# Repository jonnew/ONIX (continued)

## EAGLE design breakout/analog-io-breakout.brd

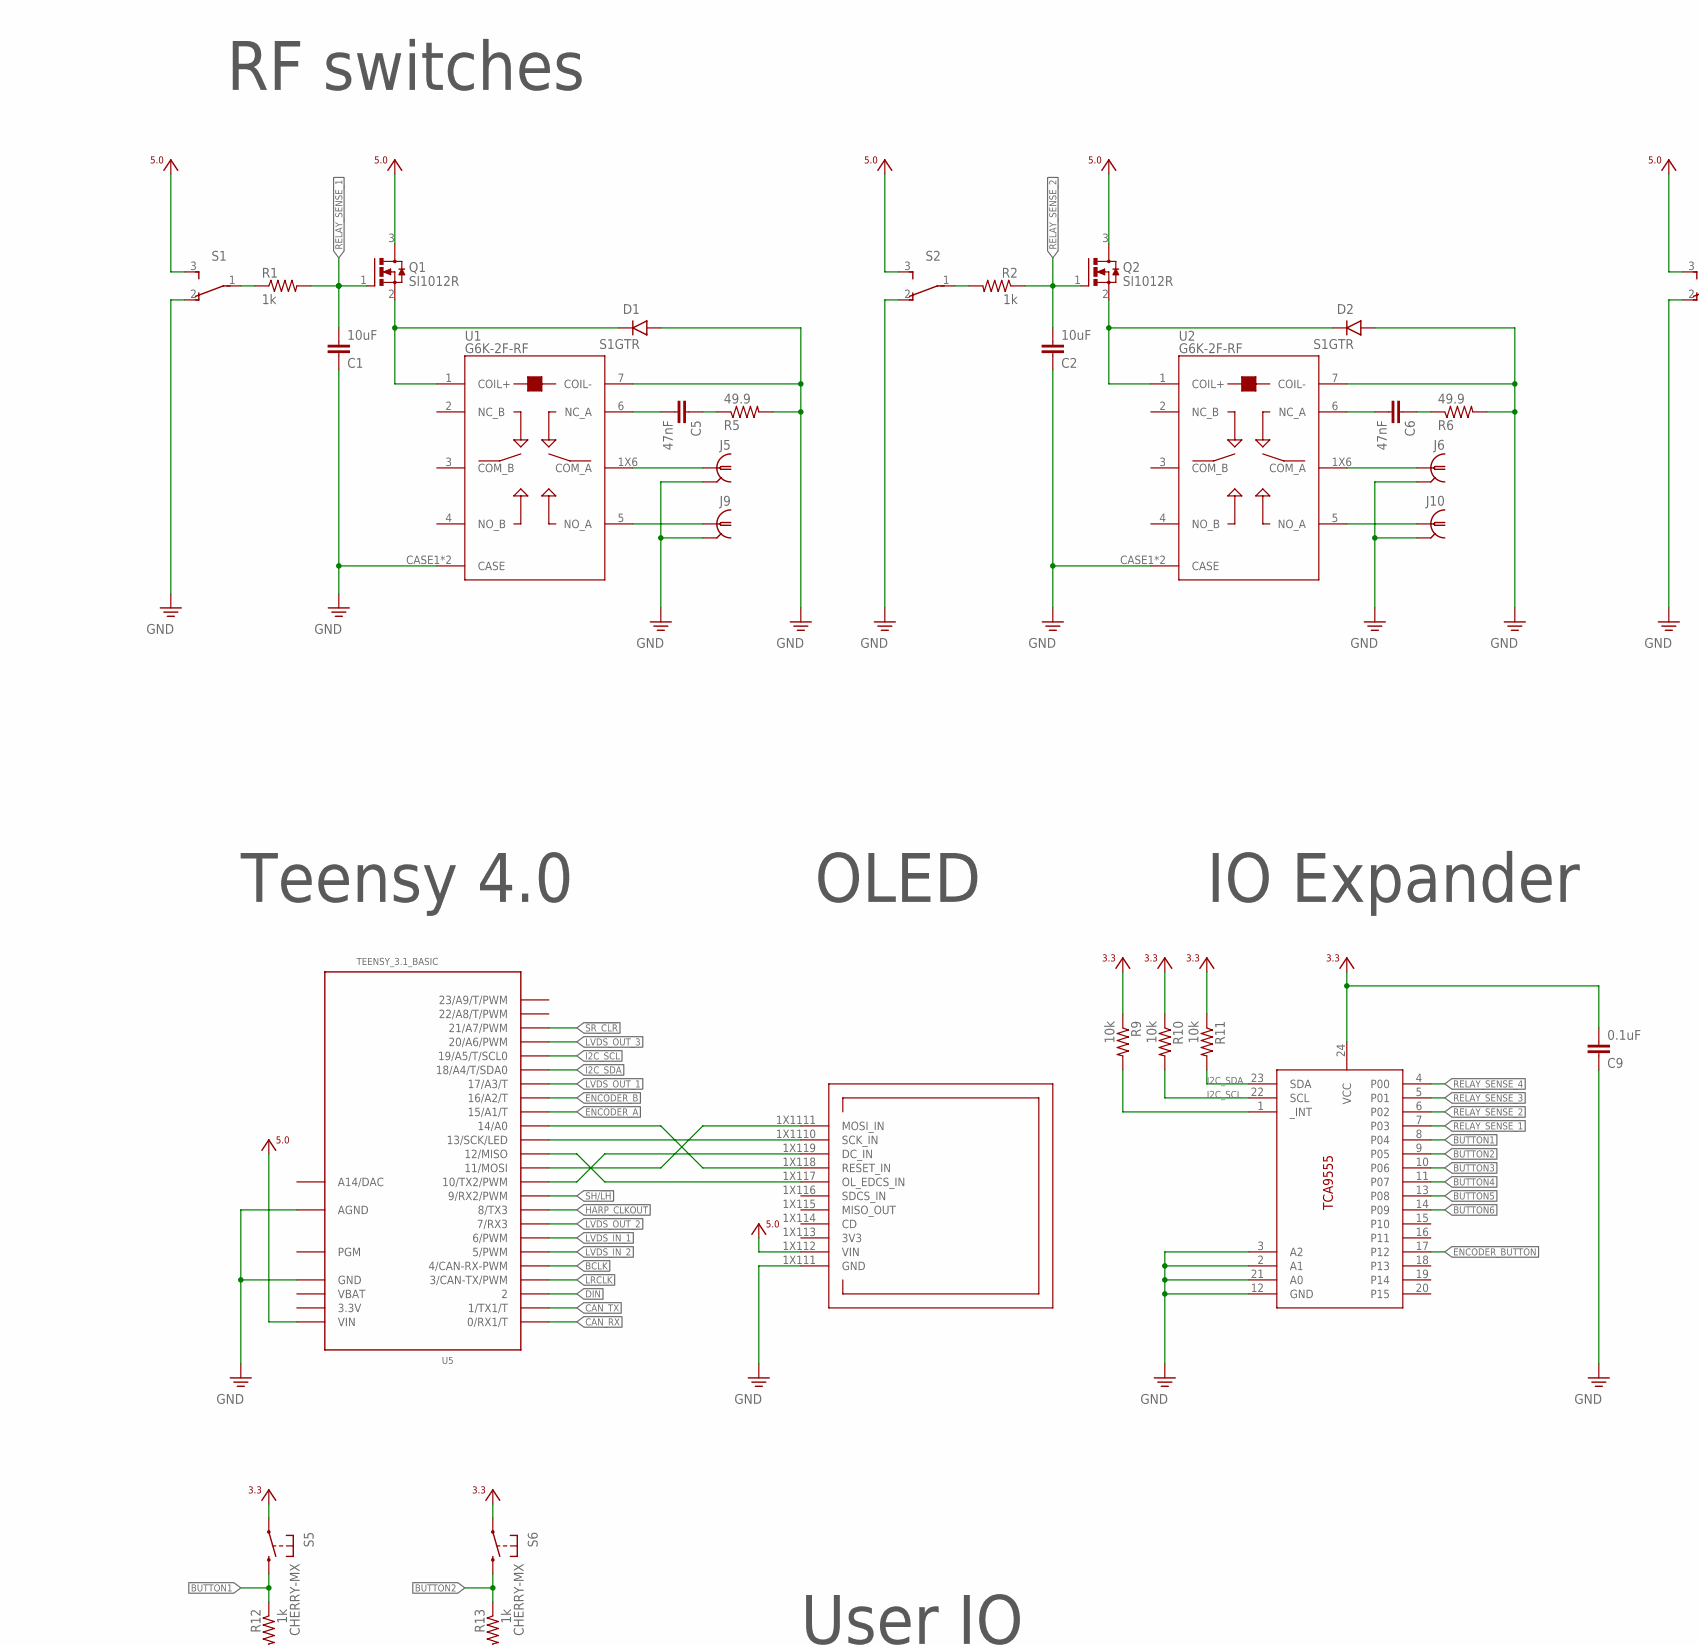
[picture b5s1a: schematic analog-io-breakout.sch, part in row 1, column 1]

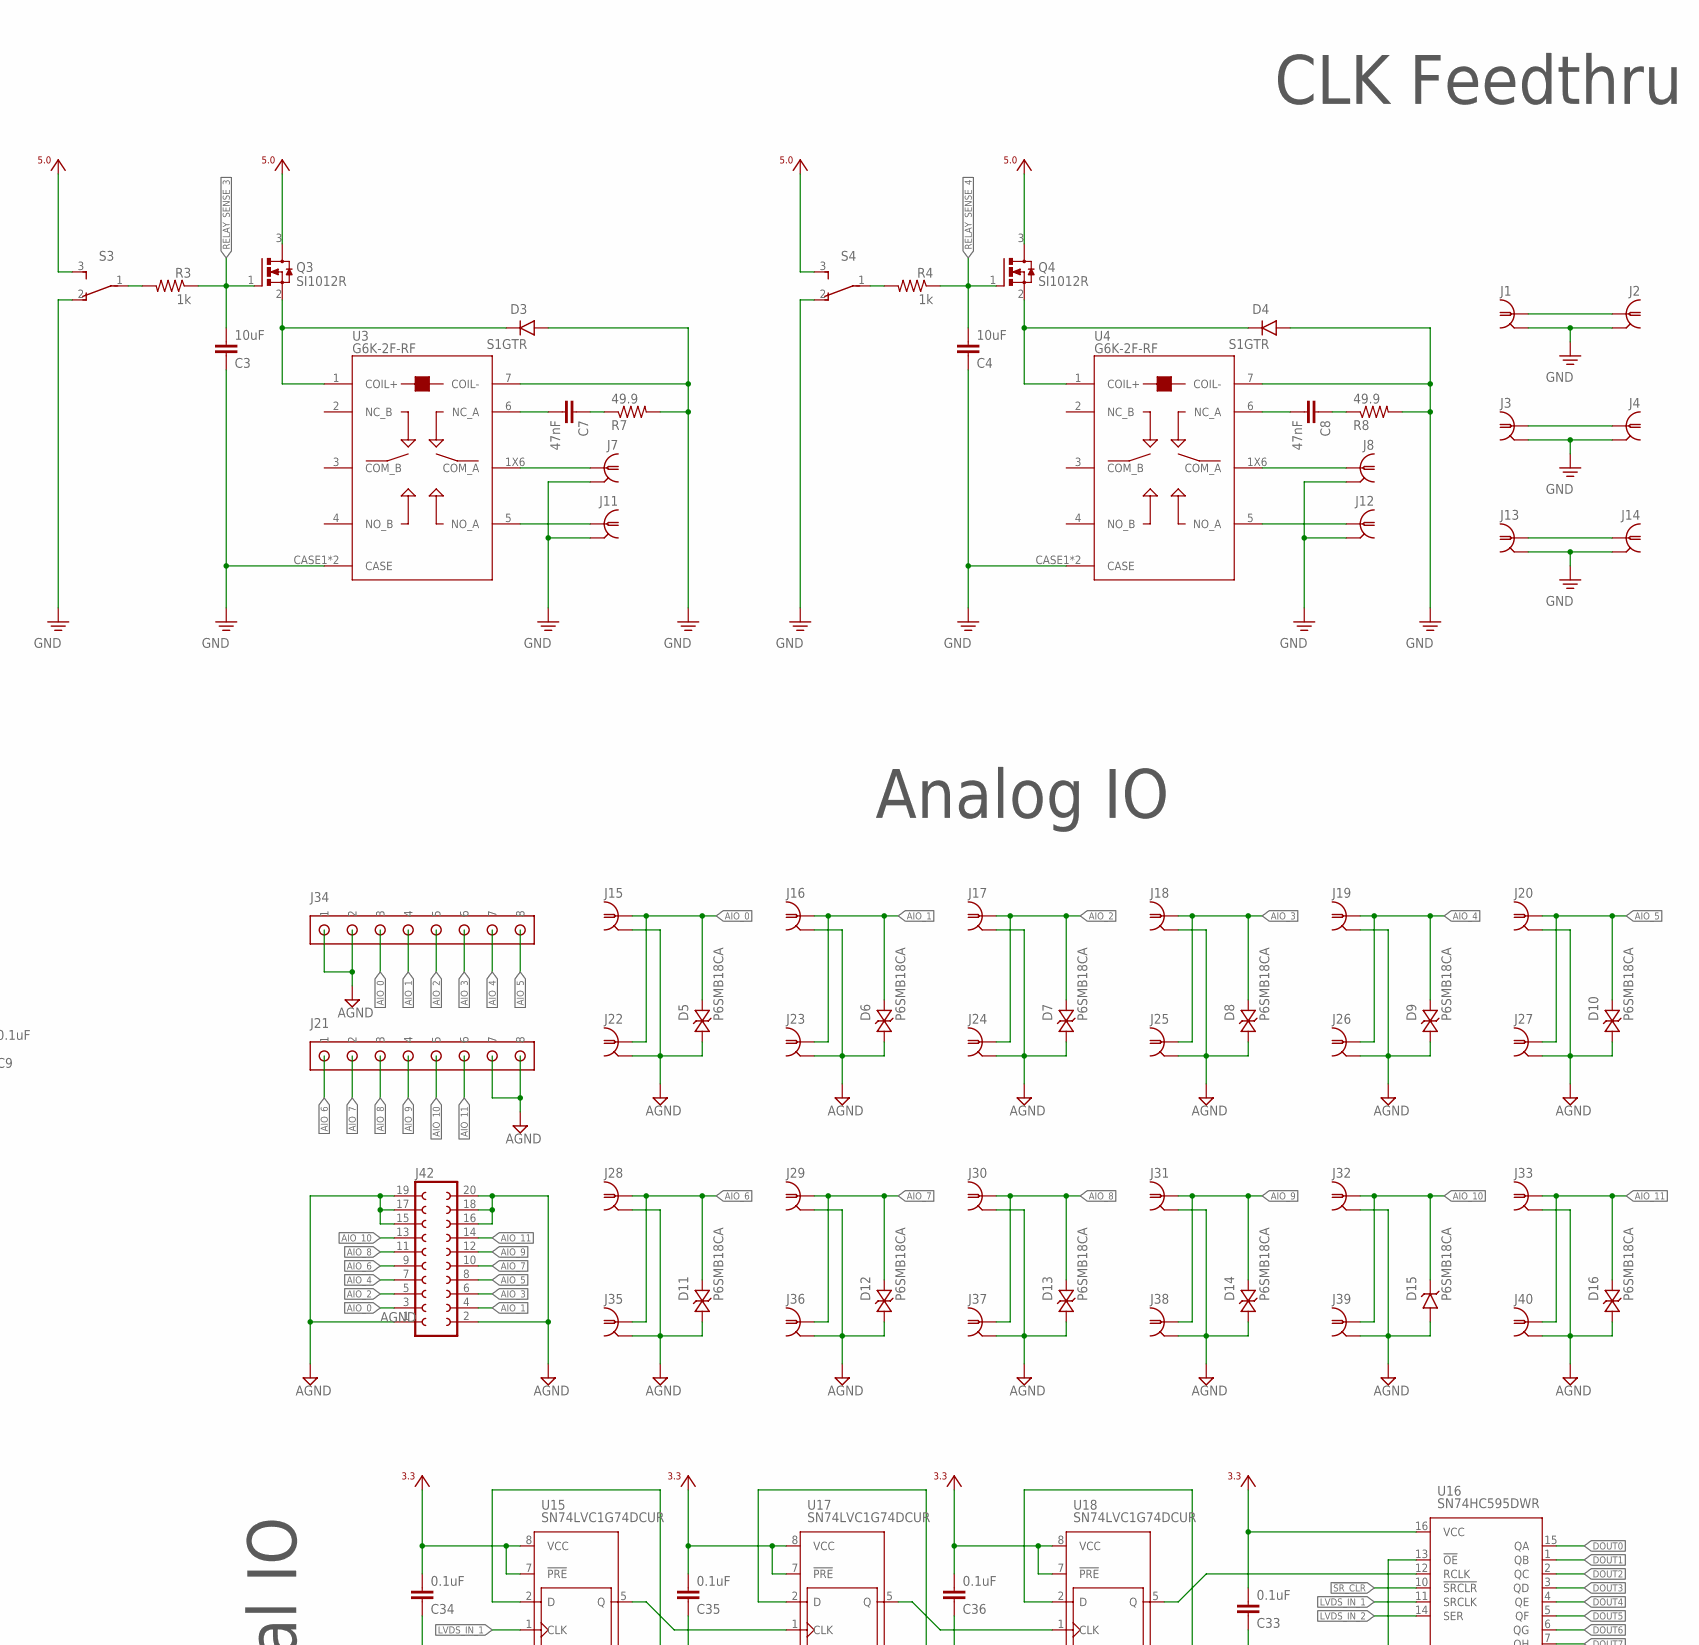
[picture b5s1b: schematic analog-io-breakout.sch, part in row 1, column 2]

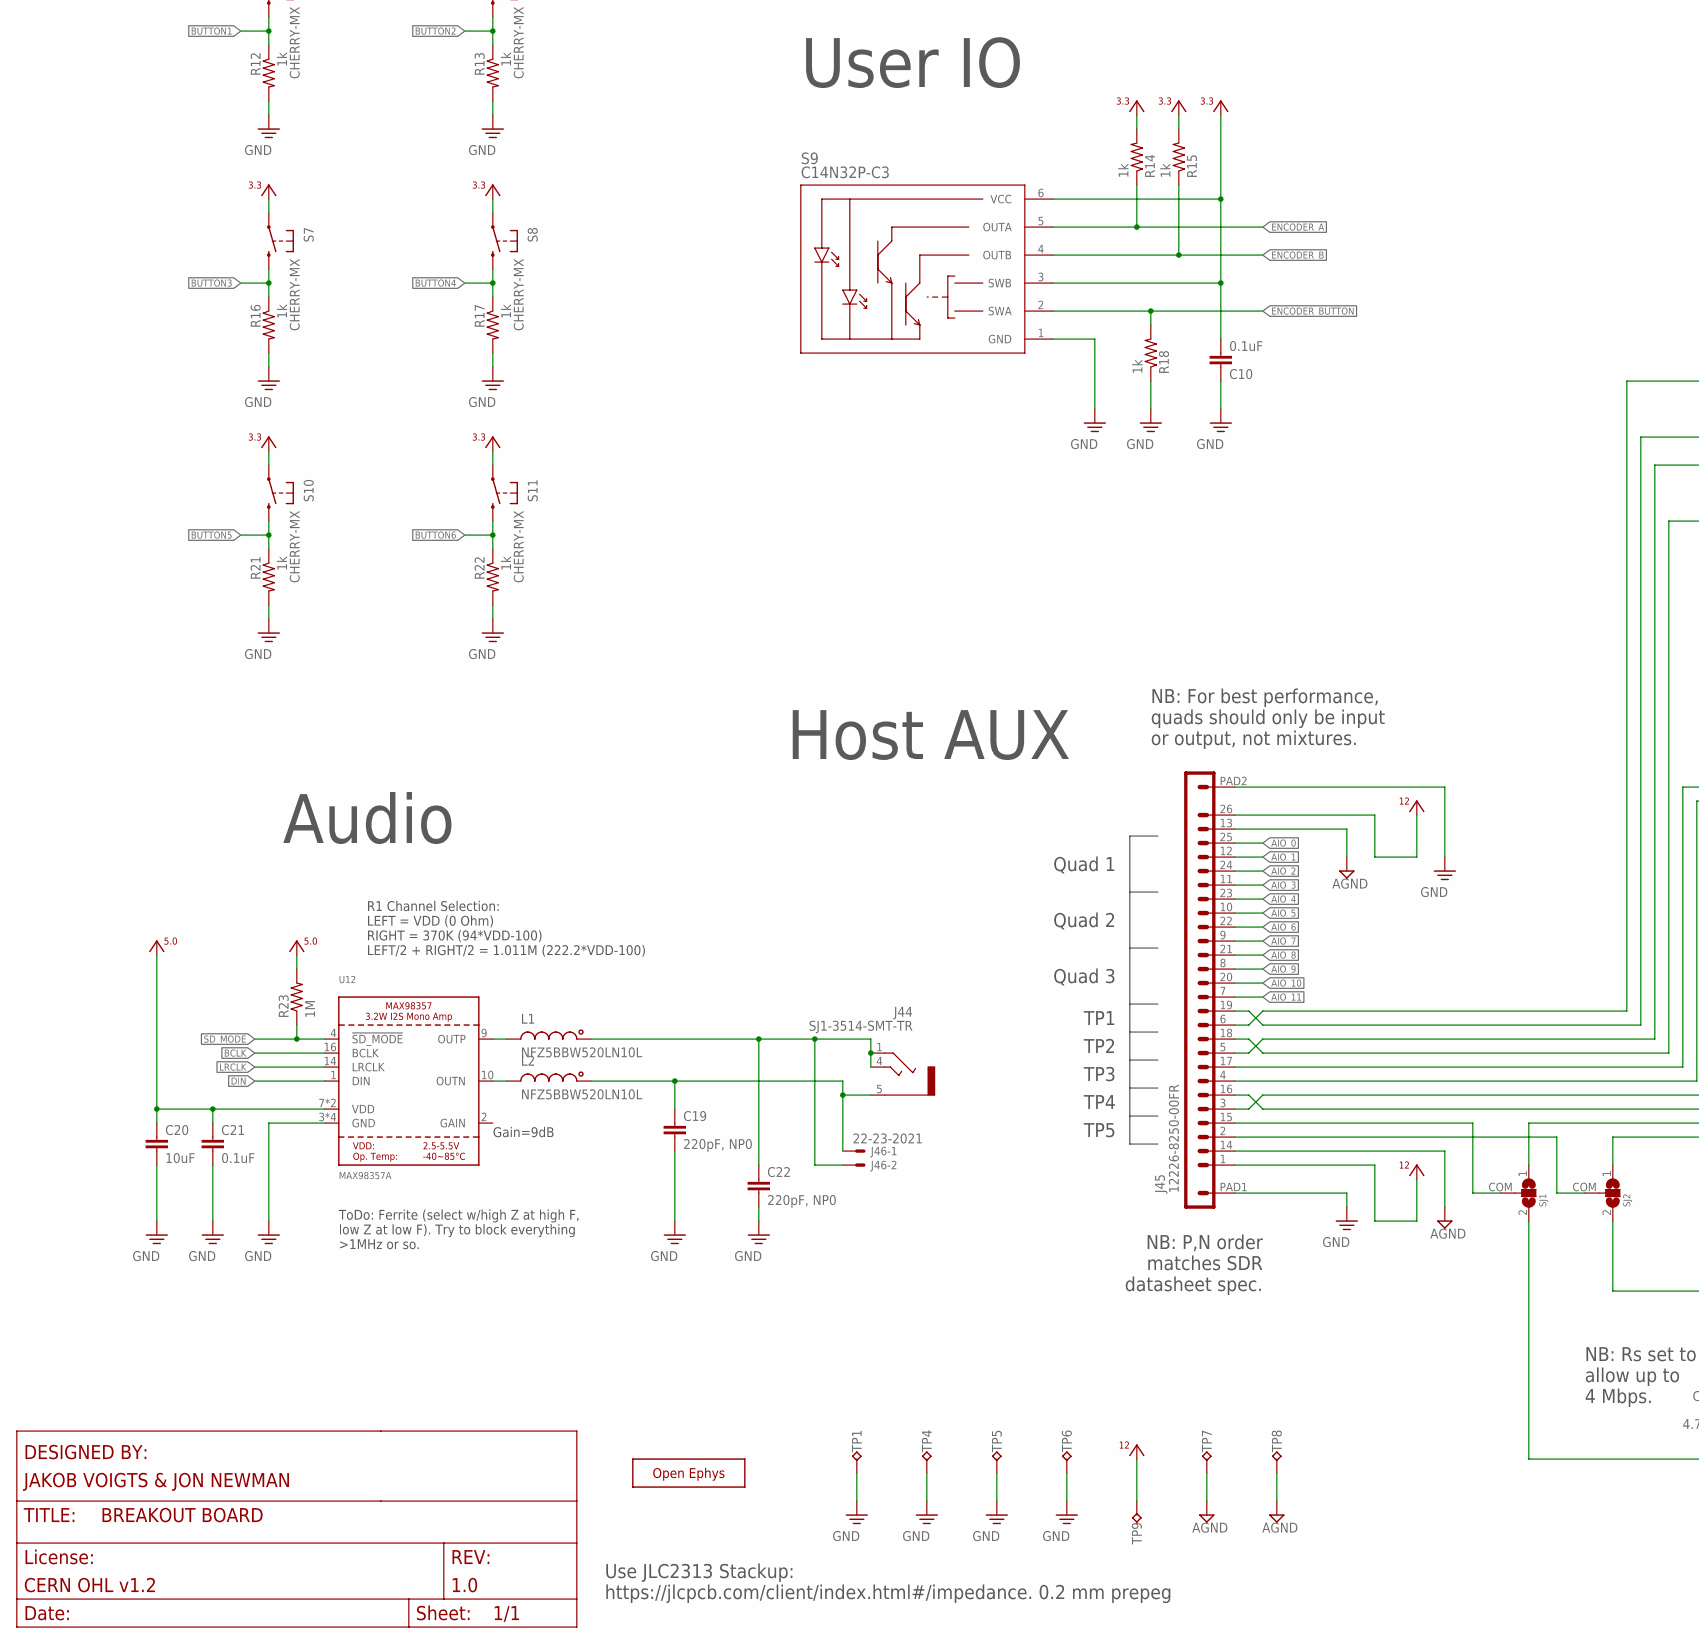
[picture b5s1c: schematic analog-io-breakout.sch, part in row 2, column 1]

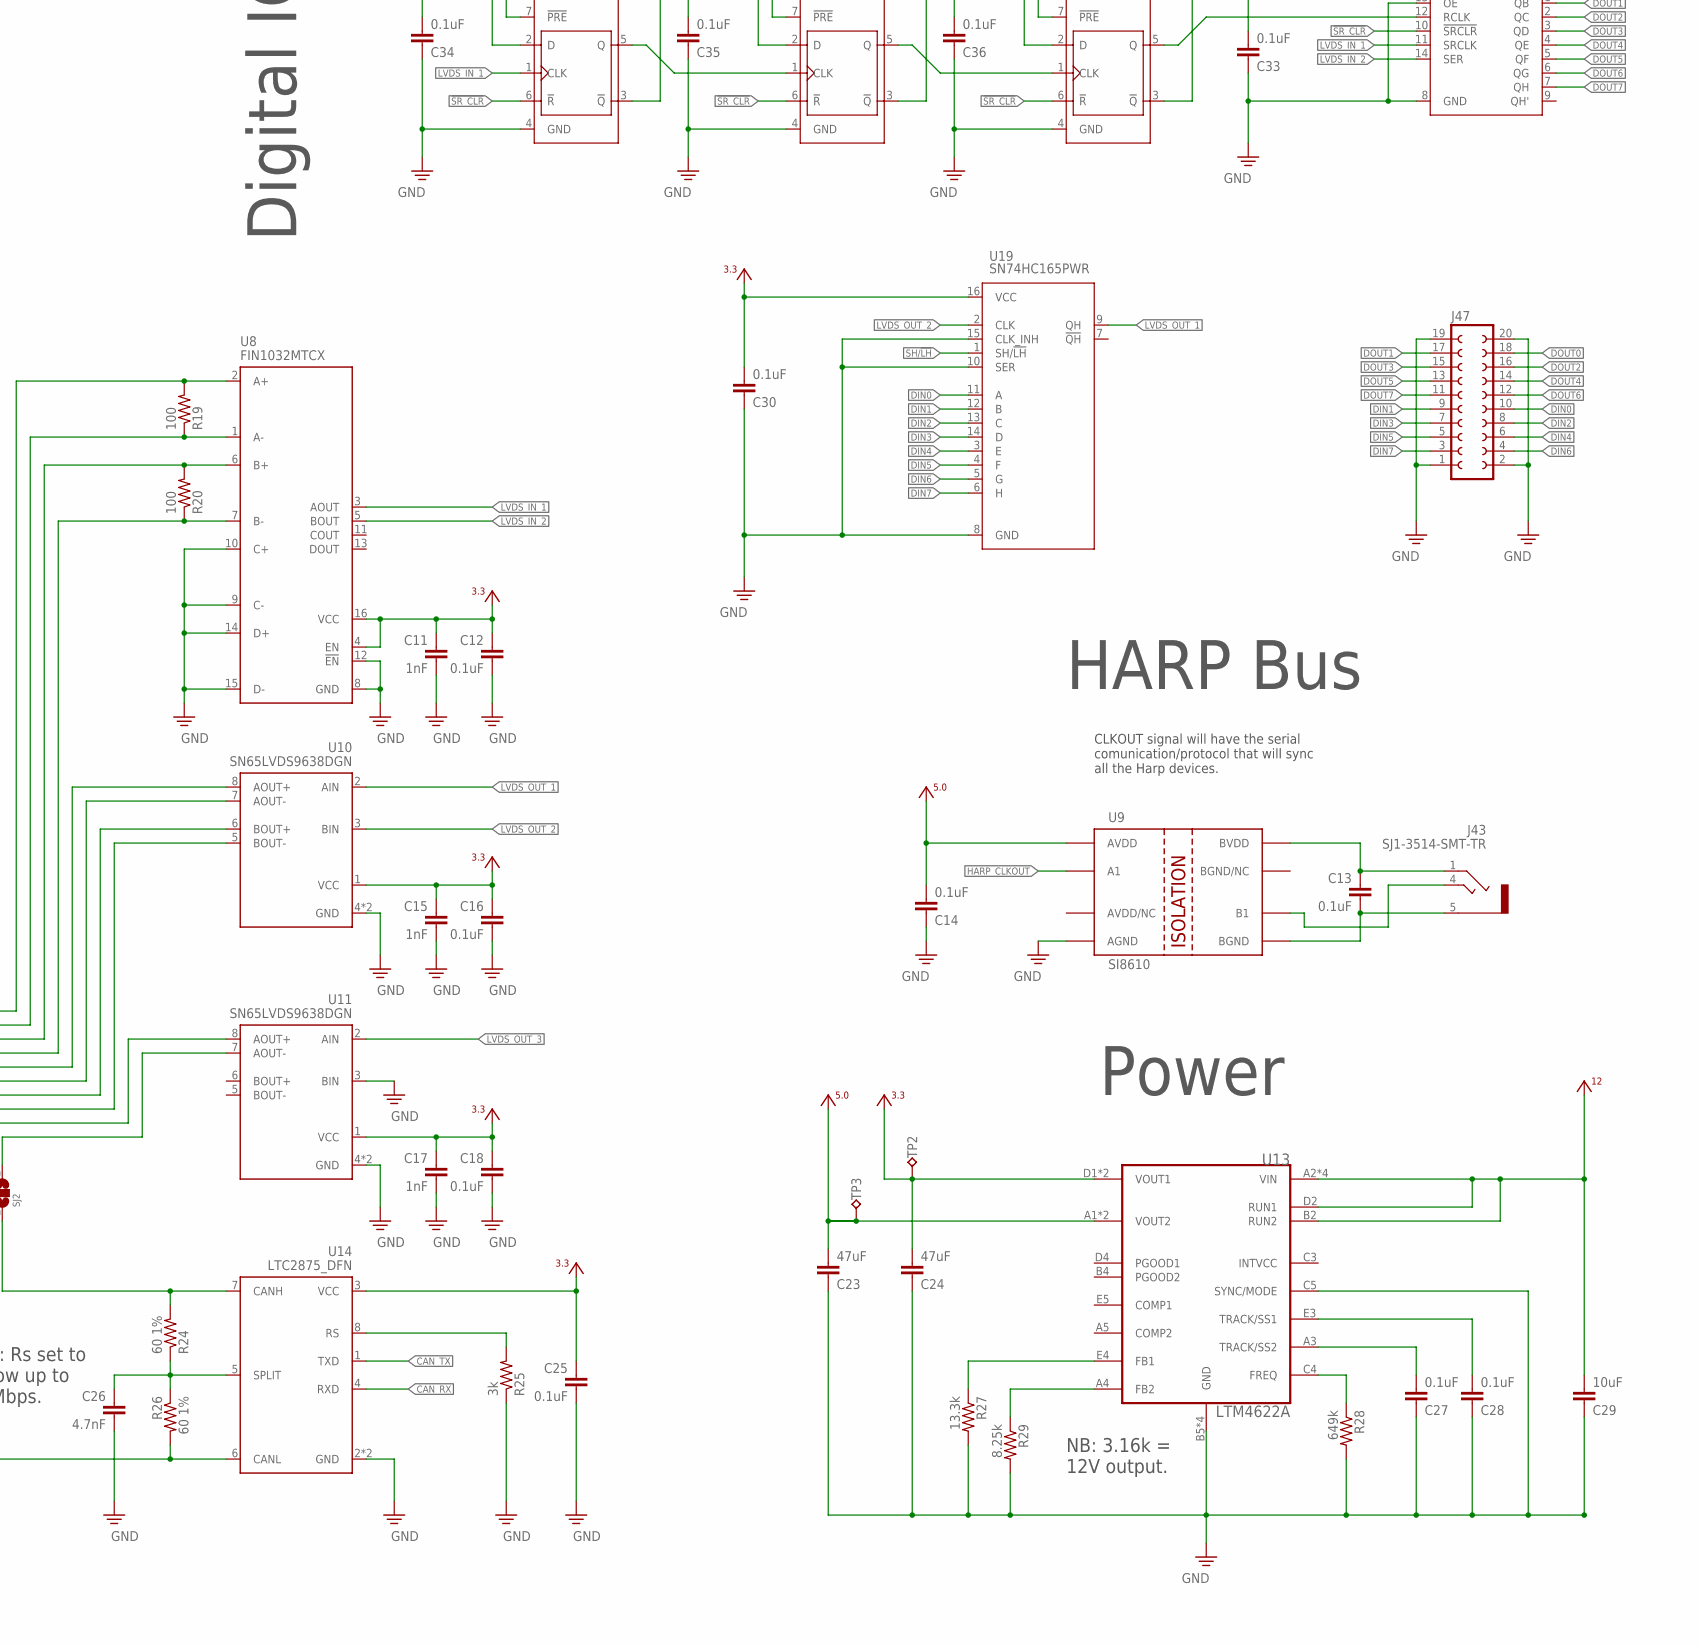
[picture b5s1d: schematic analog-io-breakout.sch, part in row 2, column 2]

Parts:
C1, C2, C3, C4, C20, C29: 10uF; 0805
C5, C6, C7, C8: 47nF; 0402
C9, C10, C12, C13, C14, C16, C18, C21, C25, C27, C28, C30, C33, C34, C35, C36: 0.1uF; 0402
C11, C15, C17: 1nF; 0402
C19, C22: 220pF, NP0; 0402
C23, C24: 47uF; 1210
C26: 4.7nF; 0402
D1, D2, D3, D4: S1GTR; SMA-DO214AC
D5, D6, D7, D8, D9, D10, D11, D12, D13, D14, D15, D16: P6SMB18CA; SMA-DO214AC
J1, J3, J9, J10, J11, J12, J13: COAX_MMCX-THRU; MMCX-THRU
J2, J4, J5, J6, J7, J8, J14, J22, J23, J24, J25, J26, J27, J35, J36, J37, J38, J39, J40: COAX_SMA-VERT; SMA_JACK_142-0701-201
J15, J16, J17, J18, J19, J20, J28, J29, J30, J31, J32, J33: COAX_0731010360; 0731010360
J21, J34: SCREW8
J42, J47: FE10-2
J43, J44: SJ1-3514-SMT-TR; 35RASMT2BHNTRX
J45: 12226-8250-00FR; 12226-82X0-00XX
J46: 22-23-2021
L1, L2: NFZ5BBW520LN10L; 2020
Q1, Q2, Q3, Q4: SI1012R; SC75
R1, R2, R3, R4, R12, R13, R14, R15, R16, R17, R18, R21, R22: 1k; 0402
R5, R6, R7, R8: 49.9; 0402
R9, R10, R11: 10k; 0402
R19, R20: 100; 0402
R23: 1M; 0402
R24, R26: 60 1%; 0402
R25: 3k; 0402
R27: 13.3k; 0402
R28: 649k; 0402
R29: 8.25k; 0402
S1, S2, S3, S4: SPDT_CK-710; CK_7101J1V3QE2
S5, S6, S7, S8, S10, S11: CHERRY-MX
S9: C14N32P-C3
SJ1, SJ2: SJ2_0201; SJ_2_0201
TP1, TP4, TP5, TP6, TP7, TP8: TP_2MM; TESTPOINT_2MM
TP2, TP3: TPB1,27; B1,27
TP9: TPTP12R; TP12R
U1, U2, U3, U4: G6K-2F-RF; G6KU-2F-RF
U5: TEENSY_3.1_BASIC
U6: ADAFRUIT_1_5_OLED
U7: TCA9555; TSSOP-24
U8: FIN1032MTCX; TSSOP-16
U9: SI8610; SO-08
U10, U11: SN65LVDS9638DGN; MSOP-8-PAD-3X3
U12: MAX98357A; QFN16_3MM
U13: LTM4622A; BGA_5X5_625X625
U14: LTC2875_DFN; DFN83X3
U15, U17, U18: SN74LVC1G74DCUR; VSSOP-N8-3X3
U16: SN74HC595DWR; TSSOP-16
U19: SN74HC165PWR; TSSOP-16
X: OE-LOGO_28X20; OE-LOGO-28X20

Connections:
3.3V: U5.3.3V, U5.3.3V1 (3.3V)
!SR_CLR: U5.21/A7 (21/A7/PWM), U15.6 (!R), U16.10 (!SRCLR), U17.6 (!R), U18.6 (!R)
+3V3: C9.2, C10.2, C11.1, C12.1, C15.1, C16.1, C17.1, C18.1, C24.2, C25.1, C30.2, C33.2, C34.2, C35.2, C36.2, R9.1, R10.1, R11.1, R14.2, R15.2, S5.SW1, S6.SW1, S7.SW1, S8.SW1, S9.3 (SWB), S9.6 (VCC), S10.SW1, S11.SW1, TP2.TP, U7.24 (VCC), U8.4 (EN), U8.16 (VCC), U10.1 (VCC), U11.1 (VCC), U13.D1 (VOUT1), U13.E1 (VOUT1), U14.3 (VCC), U15.7 (!PRE), U15.8 (VCC), U16.16 (VCC), U17.7 (!PRE), U17.8 (VCC), U18.7 (!PRE), U18.8 (VCC), U19.16 (VCC)
+5V0: C14.2, C20.1, C21.1, C23.2, Q1.3 (D), Q2.3 (D), Q3.3 (D), Q4.3 (D), R23.2, S1.3, S2.3, S3.3, S4.3, TP3.TP, U5.VIN, U6.1X112 (VIN), U9.1 (AVDD), U12.7 (VDD), U12.8 (VDD), U13.A1 (VOUT2), U13.B1 (VOUT2)
+12V: C29.2, J45.1, J45.26, TP9.TP, U13.A2 (VIN), U13.B2 (RUN2), U13.B3 (VIN), U13.D2 (RUN1), U13.D3 (VIN), U13.E2 (VIN)
AGND: D5.A (1), D6.A (1), D7.A (1), D8.A (1), D9.A (1), D10.A (1), D11.A (1), D12.A (1), D13.A (1), D14.A (1), D15.A, D16.A (1), J15.2, J15.3 (2), J15.4 (2), J15.5 (2), J16.2, J16.3 (2), J16.4 (2), J16.5 (2), J17.2, J17.3 (2), J17.4 (2), J17.5 (2), J18.2, J18.3 (2), J18.4 (2), J18.5 (2), J19.2, J19.3 (2), J19.4 (2), J19.5 (2), J20.2, J20.3 (2), J20.4 (2), J20.5 (2), J21.7, J21.8, J22.GND$1 (2), J22.GND$2 (2), J22.GND$3 (2), J22.GND$4 (2), J23.GND$1 (2), J23.GND$2 (2), J23.GND$3 (2), J23.GND$4 (2), J24.GND$1 (2), J24.GND$2 (2), J24.GND$3 (2), J24.GND$4 (2), J25.GND$1 (2), J25.GND$2 (2), J25.GND$3 (2), J25.GND$4 (2), J26.GND$1 (2), J26.GND$2 (2), J26.GND$3 (2), J26.GND$4 (2), J27.GND$1 (2), J27.GND$2 (2), J27.GND$3 (2), J27.GND$4 (2), J28.2, J28.3 (2), J28.4 (2), J28.5 (2), J29.2, J29.3 (2), J29.4 (2), J29.5 (2), J30.2, J30.3 (2), J30.4 (2), J30.5 (2), J31.2, J31.3 (2), J31.4 (2), J31.5 (2), J32.2, J32.3 (2), J32.4 (2), J32.5 (2), J33.2, J33.3 (2), J33.4 (2), J33.5 (2), J34.1, J34.2, J35.GND$1 (2), J35.GND$2 (2), J35.GND$3 (2), J35.GND$4 (2), J36.GND$1 (2), J36.GND$2 (2), J36.GND$3 (2), J36.GND$4 (2), J37.GND$1 (2), J37.GND$2 (2), J37.GND$3 (2), J37.GND$4 (2), J38.GND$1 (2), J38.GND$2 (2), J38.GND$3 (2), J38.GND$4 (2), J39.GND$1 (2), J39.GND$2 (2), J39.GND$3 (2), J39.GND$4 (2), J40.GND$1 (2), J40.GND$2 (2), J40.GND$3 (2), J40.GND$4 (2), J42.1, J42.2, J42.15, J42.16, J42.17, J42.18, J42.19, J42.20, J45.13, J45.14, TP7.1, TP8.1
AIO_0: D5.C (2), J15.1, J22.CLK (1), J34.3, J42.3, J45.25
AIO_1: D6.C (2), J16.1, J23.CLK (1), J34.4, J42.4, J45.12
AIO_2: D7.C (2), J17.1, J24.CLK (1), J34.5, J42.5, J45.24
AIO_3: D8.C (2), J18.1, J25.CLK (1), J34.6, J42.6, J45.11
AIO_4: D9.C (2), J19.1, J26.CLK (1), J34.7, J42.7, J45.23
AIO_5: D10.C (2), J20.1, J27.CLK (1), J34.8, J42.8, J45.10
AIO_6: D11.C (2), J21.1, J28.1, J35.CLK (1), J42.9, J45.22
AIO_7: D12.C (2), J21.2, J29.1, J36.CLK (1), J42.10, J45.9
AIO_8: D13.C (2), J21.3, J30.1, J37.CLK (1), J42.11, J45.21
AIO_9: D14.C (2), J21.4, J31.1, J38.CLK (1), J42.12, J45.8
AIO_10: D15.C, J21.5, J32.1, J39.CLK (1), J42.13, J45.20
AIO_11: D16.C (2), J21.6, J33.1, J40.CLK (1), J42.14, J45.7
BCLK: U5.4 (4/CAN-RX-PWM), U12.16 (BCLK)
BUTTON1: R12.1, S5.SW2 (S), U7.8 (P04)
BUTTON2: R13.1, S6.SW2 (S), U7.9 (P05)
BUTTON3: R16.1, S7.SW2 (S), U7.10 (P06)
BUTTON4: R17.1, S8.SW2 (S), U7.11 (P07)
BUTTON5: R21.1, S10.SW2 (S), U7.13 (P08)
BUTTON6: R22.1, S11.SW2 (S), U7.14 (P09)
CAN_N: R26.2, SJ1.2, U14.6 (CANL)
CAN_P: R24.2, SJ2.2, U14.7 (CANH)
CAN_RX: U5.0 (0/RX1/T), U14.4 (RXD)
CAN_TX: U5.1 (1/TX1/T), U14.1 (TXD)
CLK/8: U16.12 (RCLK), U18.5 (Q)
DIN: U5.2, U12.1 (DIN)
DIN0: J47.10, U19.11 (A)
DIN1: J47.9, U19.12 (B)
DIN2: J47.8, U19.13 (C)
DIN3: J47.7, U19.14 (D)
DIN4: J47.6, U19.3 (E)
DIN5: J47.5, U19.4 (F)
DIN6: J47.4, U19.5 (G)
DIN7: J47.3, U19.6 (H)
DOUT0: J47.18, U16.15 (QA)
DOUT1: J47.17, U16.1 (QB)
DOUT2: J47.16, U16.2 (QC)
DOUT3: J47.15, U16.3 (QD)
DOUT4: J47.14, U16.4 (QE)
DOUT5: J47.13, U16.5 (QF)
DOUT6: J47.12, U16.6 (QG)
DOUT7: J47.11, U16.7 (QH)
ENCODER_A: R14.1, S9.5 (OUTA), U5.15/A1 (15/A1/T)
ENCODER_B: R15.1, S9.4 (OUTB), U5.16/A2 (16/A2/T)
ENCODER_BUTTON: R18.2, S9.2 (SWA), U7.17 (P12)
GND: C1.1, C2.1, C3.1, C4.1, C9.1, C10.1, C11.2, C12.2, C14.1, C15.2, C16.2, C17.2, C18.2, C19.2, C20.2, C21.2, C22.2, C23.1, C24.1, C25.2, C26.2, C27.1, C28.1, C29.1, C30.1, C33.1, C34.1, C35.1, C36.1, D1.A, D2.A, D3.A, D4.A, J1.GND@1 (2), J1.GND@2 (2), J1.GND@3 (2), J1.GND@4 (2), J2.GND$1 (2), J2.GND$2 (2), J2.GND$3 (2), J2.GND$4 (2), J3.GND@1 (2), J3.GND@2 (2), J3.GND@3 (2), J3.GND@4 (2), J4.GND$1 (2), J4.GND$2 (2), J4.GND$3 (2), J4.GND$4 (2), J5.GND$1 (2), J5.GND$2 (2), J5.GND$3 (2), J5.GND$4 (2), J6.GND$1 (2), J6.GND$2 (2), J6.GND$3 (2), J6.GND$4 (2), J7.GND$1 (2), J7.GND$2 (2), J7.GND$3 (2), J7.GND$4 (2), J8.GND$1 (2), J8.GND$2 (2), J8.GND$3 (2), J8.GND$4 (2), J9.GND@1 (2), J9.GND@2 (2), J9.GND@3 (2), J9.GND@4 (2), J10.GND@1 (2), J10.GND@2 (2), J10.GND@3 (2), J10.GND@4 (2), J11.GND@1 (2), J11.GND@2 (2), J11.GND@3 (2), J11.GND@4 (2), J12.GND@1 (2), J12.GND@2 (2), J12.GND@3 (2), J12.GND@4 (2), J13.GND@1 (2), J13.GND@2 (2), J13.GND@3 (2), J13.GND@4 (2), J14.GND$1 (2), J14.GND$2 (2), J14.GND$3 (2), J14.GND$4 (2), J45.PAD1, J45.PAD2, J47.1, J47.2, J47.19, J47.20, R5.2, R6.2, R7.2, R8.2, R12.2, R13.2, R16.2, R17.2, R18.1, R21.2, R22.2, R25.1, R27.2, R28.2, R29.2, S1.2 (1), S2.2 (1), S3.2 (1), S4.2 (1), S9.1 (GND), TP1.1, TP4.1, TP5.1, TP6.1, U1.7 (COIL-), U1.CASE1 (CASE), U1.CASE2 (CASE), U2.7 (COIL-), U2.CASE1 (CASE), U2.CASE2 (CASE), U3.7 (COIL-), U3.CASE1 (CASE), U3.CASE2 (CASE), U4.7 (COIL-), U4.CASE1 (CASE), U4.CASE2 (CASE), U5.AGND, U5.GND, U5.GND1 (GND), U6.1X111 (GND), U7.2 (A1), U7.3 (A2), U7.12 (GND), U7.21 (A0), U8.8 (GND), U8.9 (C-), U8.10 (C+), U8.12 (!EN), U8.14 (D+), U8.15 (D-), U9.4 (AGND), U10.4 (GND), U10.PAD (GND), U11.3 (BIN), U11.4 (GND), U11.PAD (GND), U12.3 (GND), U12.11 (GND), U12.15 (GND), U12.THERMAL (GND), U13.B5 (GND), U13.C1 (GND), U13.C2 (GND), U13.C5 (SYNC/MODE), U13.D5 (GND), U14.2 (GND), U14.PAD (GND), U15.4 (GND), U16.8 (GND), U16.13 (!OE), U17.4 (GND), U18.4 (GND), U19.8 (GND), U19.10 (SER), U19.15 (CLK_INH)
HARP_CLKOUT: U5.8 (8/TX3), U9.2 (A1)
I2C_SCL: R10.2, U5.19/A5 (19/A5/T/SCL0), U7.22 (SCL)
I2C_SDA: R11.2, U5.18/A4 (18/A4/T/SDA0), U7.23 (SDA)
LRCLK: U5.3 (3/CAN-TX/PWM), U12.14 (LRCLK)
LVDS_DIN0_N1: J45.4, U10.7 (AOUT-)
LVDS_DIN0_P1: J45.17, U10.8 (AOUT+)
LVDS_DIN1_N1: J45.16, U10.5 (BOUT-)
LVDS_DIN1_P1: J45.3, U10.6 (BOUT+)
LVDS_DIN2_N: SJ2.1, U11.7 (AOUT-)
LVDS_DIN2_P: SJ1.1, U11.8 (AOUT+)
LVDS_DOUT0_N1: J45.19, R19.1, U8.1 (A-)
LVDS_DOUT0_P1: J45.6, R19.2, U8.2 (A+)
LVDS_DOUT1_N1: J45.18, R20.1, U8.7 (B-)
LVDS_DOUT1_P1: J45.5, R20.2, U8.6 (B+)
LVDS_IN_1: U5.6 (6/PWM), U8.3 (AOUT), U15.1 (CLK), U16.11 (SRCLK)
LVDS_IN_2: U5.5 (5/PWM), U8.5 (BOUT), U16.14 (SER)
LVDS_OUT_1: U5.17/A3 (17/A3/T), U10.2 (AIN), U19.9 (QH)
LVDS_OUT_2: U5.7 (7/RX3), U10.3 (BIN), U19.2 (CLK)
LVDS_OUT_3: U5.20/A6 (20/A6/PWM), U11.2 (AIN)
unnamed: J1.SIG (1), J2.CLK (1)
unnamed: U5.11 (11/MOSI), U6.1X1111 (MOSI_IN)
unnamed: J3.SIG (1), J4.CLK (1)
unnamed: J13.SIG (1), J14.CLK (1)
unnamed: D1.C, Q1.2 (S), U1.1 (COIL+)
unnamed: U5.13 (13/SCK/LED), U6.1X1110 (SCK_IN)
unnamed: U5.10 (10/TX2/PWM), U6.1X119 (DC_IN)
unnamed: U5.14/A0, U6.1X118 (RESET_IN)
unnamed: U5.12 (12/MISO), U6.1X117 (OL_EDCS_IN)
unnamed: L2.2, U12.10 (OUTN)
unnamed: J45.2, SJ2.COM
unnamed: J45.15, SJ1.COM
unnamed: R25.2, U14.8 (RS)
unnamed: L1.2, U12.9 (OUTP)
unnamed: C5.2, U1.6 (NC_A)
unnamed: C13.1, J43.1, U9.8 (BVDD)
unnamed: C13.2, J43.5, U9.5 (BGND)
unnamed: J43.4, U9.6 (B1)
unnamed: J10.SIG (1), U2.5 (NO_A)
unnamed: U15.2 (D), U15.3 (!Q)
unnamed: U15.5 (Q), U17.1 (CLK)
unnamed: C6.1, R6.1
unnamed: R1.1, S1.1 (2)
unnamed: R29.1, U13.A4 (FB2)
unnamed: R27.1, U13.E4 (FB1)
unnamed: C27.2, U13.A3 (TRACK/SS2)
unnamed: C28.2, U13.E3 (TRACK/SS1)
unnamed: J9.SIG (1), U1.5 (NO_A)
unnamed: J5.CLK (1), U1.1X6 (COM_A)
unnamed: C5.1, R5.1
unnamed: C6.2, U2.6 (NC_A)
unnamed: D3.C, Q3.2 (S), U3.1 (COIL+)
unnamed: C7.1, R7.1
unnamed: J6.CLK (1), U2.1X6 (COM_A)
unnamed: R2.2, S2.1 (2)
unnamed: C7.2, U3.6 (NC_A)
unnamed: J11.SIG (1), U3.5 (NO_A)
unnamed: R3.2, S3.1 (2)
unnamed: D4.C, Q4.2 (S), U4.1 (COIL+)
unnamed: D2.C, Q2.2 (S), U2.1 (COIL+)
unnamed: C26.1, R24.1, R26.1, U14.5 (SPLIT)
unnamed: R9.2, U7.1 (_INT)
unnamed: J7.CLK (1), U3.1X6 (COM_A)
unnamed: R4.2, S4.1 (2)
unnamed: C8.1, R8.1
unnamed: C8.2, U4.6 (NC_A)
unnamed: J12.SIG (1), U4.5 (NO_A)
unnamed: J8.CLK (1), U4.1X6 (COM_A)
unnamed: U17.2 (D), U17.3 (!Q)
unnamed: U17.5 (Q), U18.1 (CLK)
unnamed: U18.2 (D), U18.3 (!Q)
unnamed: R28.1, U13.C4 (FREQ)
RELAY_SENSE_1: C1.2, Q1.1 (G), R1.2, U7.7 (P03)
RELAY_SENSE_2: C2.2, Q2.1 (G), R2.1, U7.6 (P02)
RELAY_SENSE_3: C3.2, Q3.1 (G), R3.1, U7.5 (P01)
RELAY_SENSE_4: C4.2, Q4.1 (G), R4.1, U7.4 (P00)
SD_MODE: R23.1, U12.4 (!SD_MODE)
SH/!LH: U5.9 (9/RX2/PWM), U19.1 (SH/!LH)
VBAT: U5.VBAT
VO+: C22.1, J44.1, J44.4, J46.2, L1.1
VO-: C19.1, J44.5, J46.1, L2.1

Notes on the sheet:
Use JLC2313 Stackup: https://jlcpcb.com/client/index.html#/impedance. 0.2 mm prepeg
Teensy 4.0
Quad 1
Quad 2
Quad 3
NB: For best performance, quads should only be input or output, not mixtures.
TP1
TP2
TP3
TP4
TP5
NB: P,N order matches SDR datasheet spec.
NB: Rs set to allow up to 4 Mbps.
NB: 3.16k = 12V output.
Power
Host AUX
RF switches
Analog IO
CLKOUT signal will have the serial comunication/protocol that will sync all the Harp devices.
HARP Bus
R1 Channel Selection: LEFT = VDD (0 Ohm) RIGHT = 370K (94*VDD-100) LEFT/2 + RIGHT/2 = 1.011M (222.2*VDD-100)
ToDo: Ferrite (select w/high Z at high F, low Z at low F). Try to block everything >1MHz or so.
Gain=9dB
Audio
IO Expander
OLED
User IO
CLK Feedthru
Digital IO

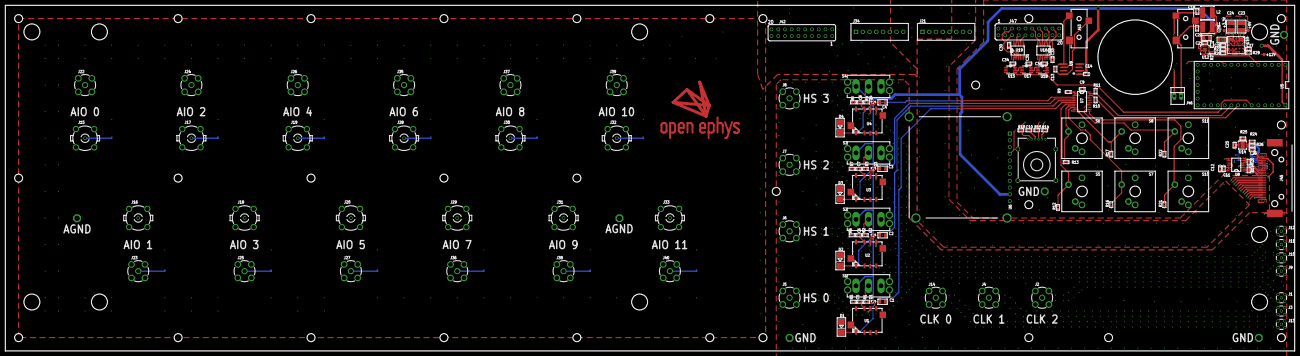
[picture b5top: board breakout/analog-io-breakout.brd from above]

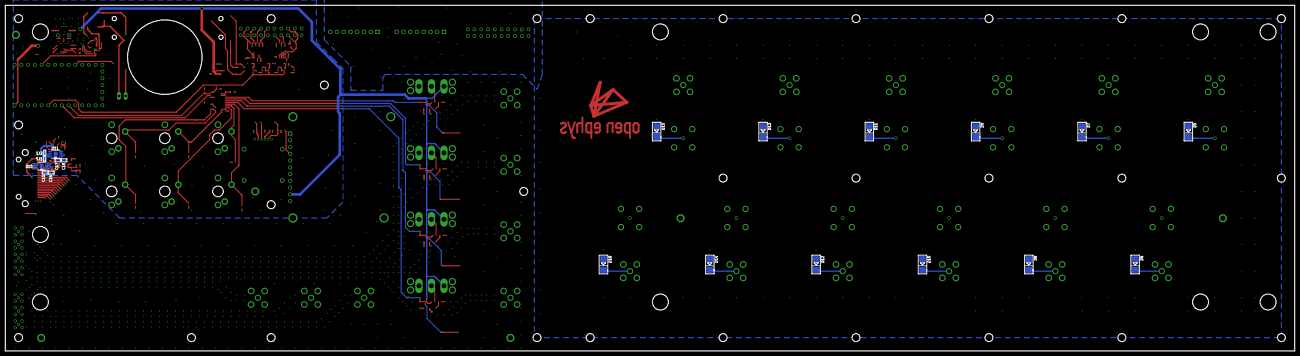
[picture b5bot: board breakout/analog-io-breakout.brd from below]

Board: 4 copper layers, 485.0 x 130.0 mm, 173 parts (20 on the bottom side), 130 nets.
